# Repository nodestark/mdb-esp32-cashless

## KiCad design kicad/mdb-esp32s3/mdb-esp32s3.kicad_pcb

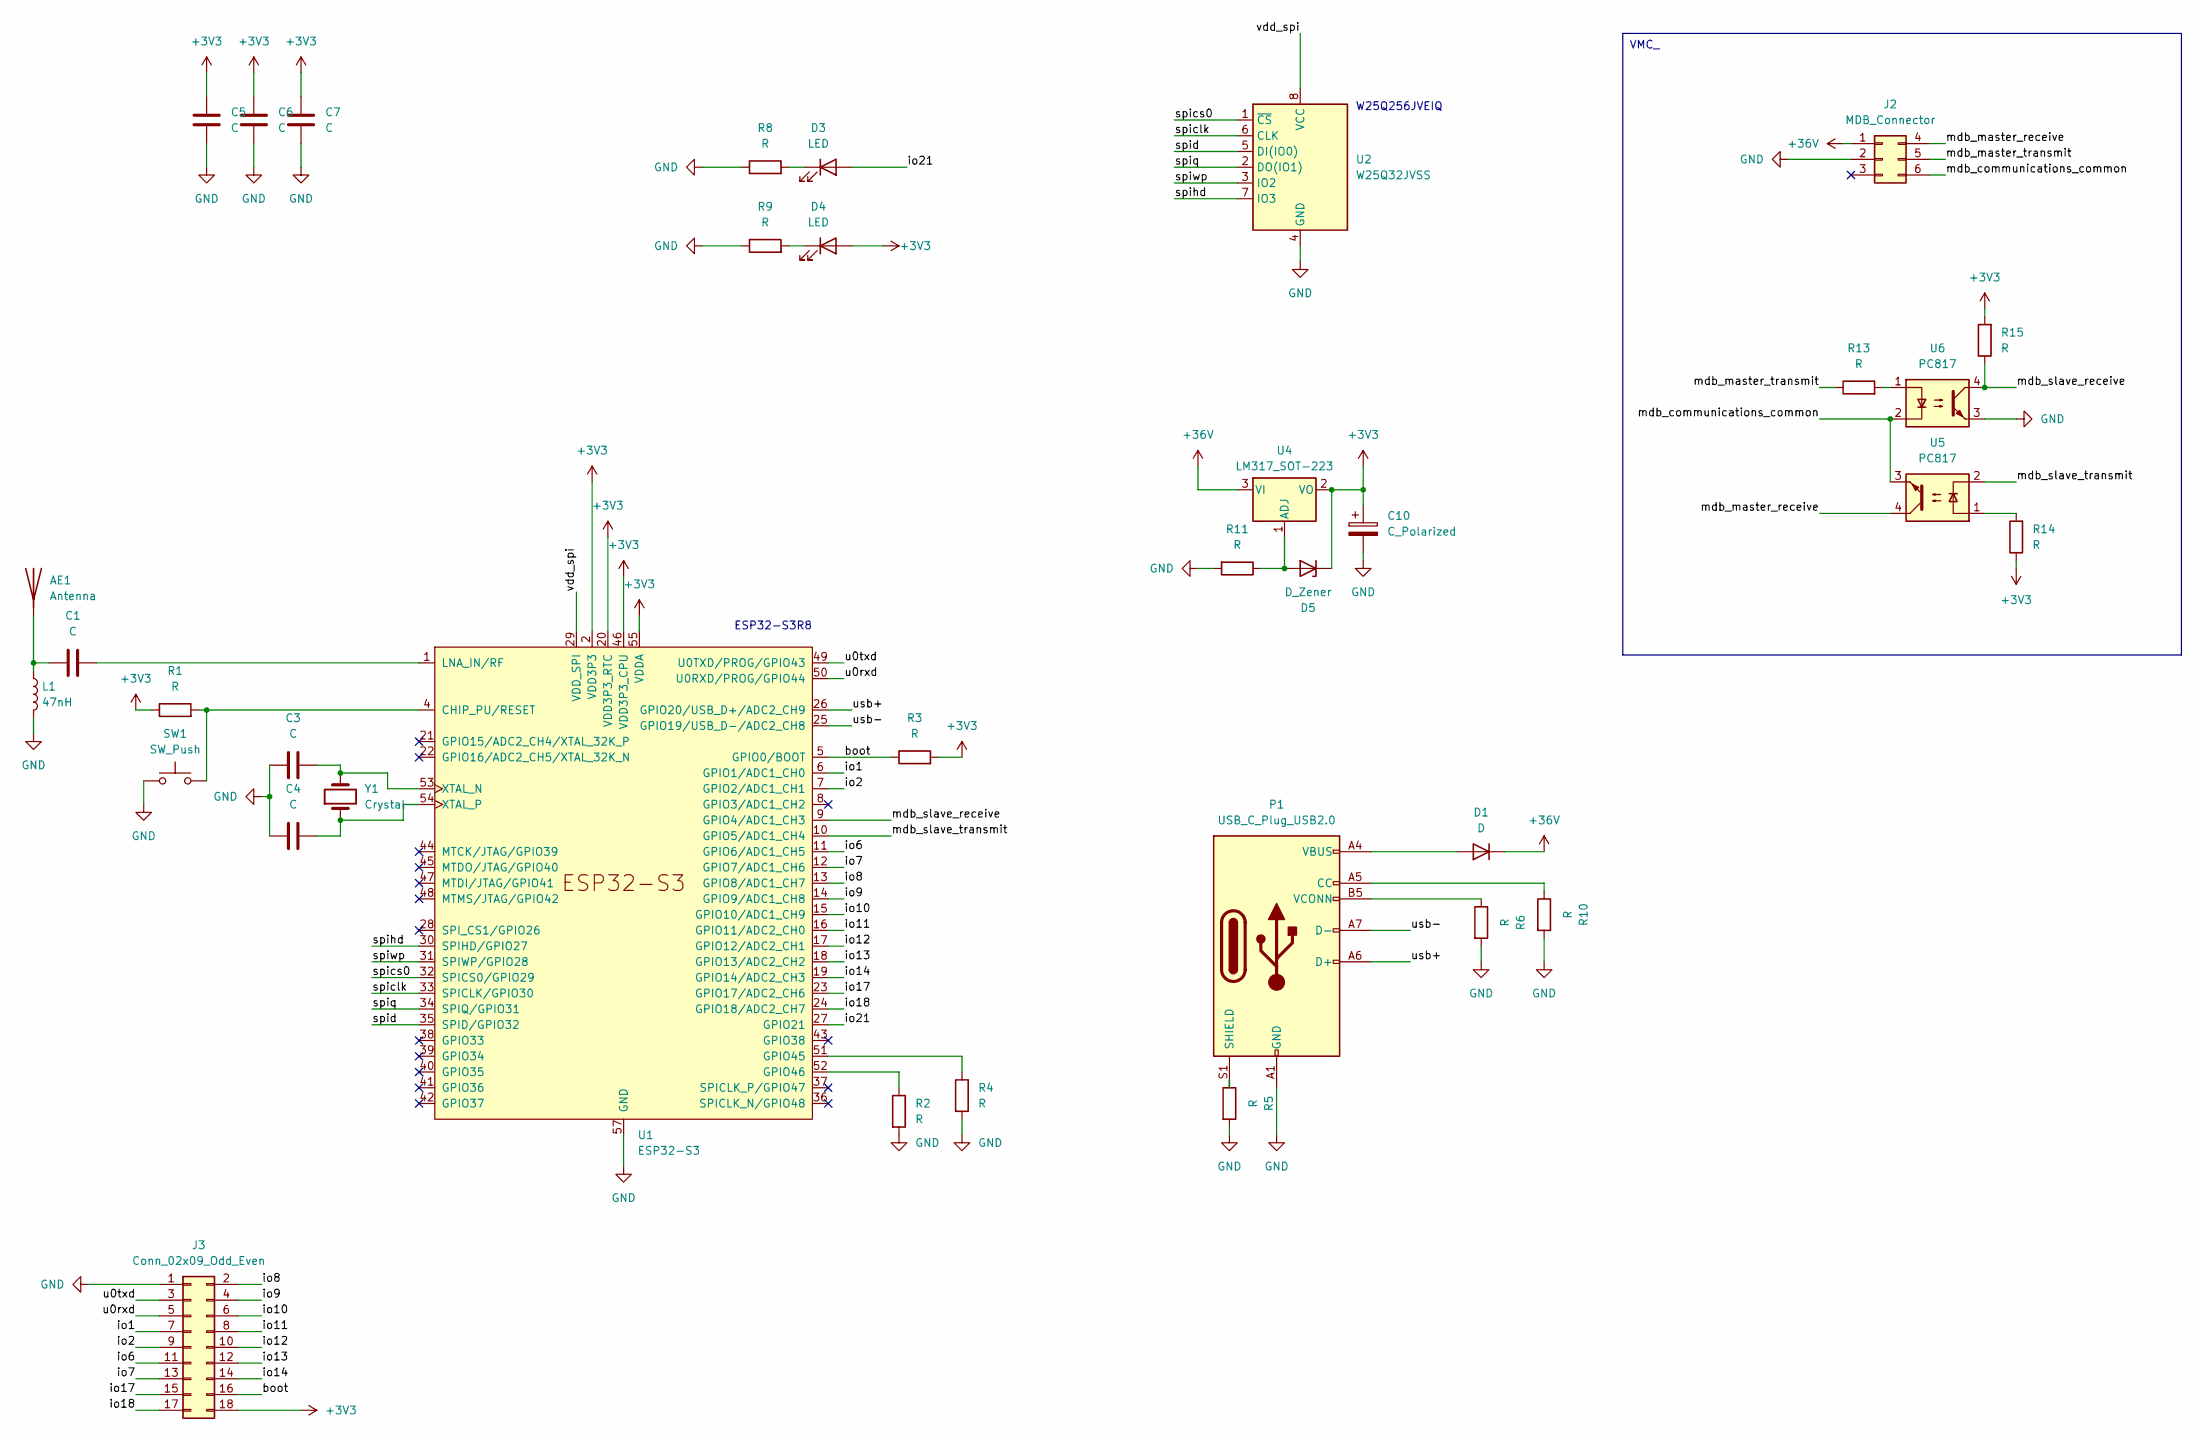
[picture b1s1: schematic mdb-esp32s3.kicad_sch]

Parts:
AE1: Antenna; Texas_SWRA117D_2.4GHz_Right
C1, C3, C4, C5, C6, C7: C; C_0603_1608Metric
C10: C_Polarized; CP_EIA-3216-18_Kemet-A
D1: D; D_SOD-123
D3, D4: LED; LED_0603_1608Metric
D5: D_Zener; D_MiniMELF
J2: MDB_Connector; Molex_Mini-Fit_Jr_5566-06A_2x03_P4.20mm_Vertical
J3: Conn_02x09_Odd_Even; PinHeader_2x09_P2.54mm_Vertical
L1: 47nH; L_0603_1608Metric
P1: USB_C_Plug_USB2.0; USB_C_Receptacle_G-Switch_GT-USB-7010ASV
R1, R2, R3, R4, R5, R6, R8, R9, R10: R; R_0603_1608Metric
R11, R13, R14, R15: R; R_0805_2012Metric
SW1: SW_Push; SW_Tactile_SPST_NO_Straight_CK_PTS636Sx25SMTRLFS
U1: ESP32-S3; QFN-56-1EP_7x7mm_P0.4mm_EP5.6x5.6mm
U2: W25Q32JVSS; WSON-8-1EP_8x6mm_P1.27mm_EP3.4x4.3mm
U4: LM317_SOT-223; SOT-223-3_TabPin2
U5, U6: PC817; DIP-4_W7.62mm
Y1: Crystal; Crystal_HC49-4H_Vertical

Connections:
+3V3: C5.2, C6.2, C7.2, C10.1, D4.2 (A), D5.1 (K), J3.18, R1.1, R3.2, R14.1, R15.2, U1.2 (VDD3P3), U1.3 (VDD3P3), U1.20 (VDD3P3_RTC), U1.46 (VDD3P3_CPU), U1.55 (VDDA), U1.56 (VDDA), U4.2 (VO)
+36V: D1.1 (K), J2.1, U4.3 (VI)
/boot: J3.16, R3.1, U1.5 (GPIO0/BOOT)
/io1: J3.7, U1.6 (GPIO1/ADC1_CH0)
/io2: J3.9, U1.7 (GPIO2/ADC1_CH1)
/io6: J3.11, U1.11 (GPIO6/ADC1_CH5)
/io7: J3.13, U1.12 (GPIO7/ADC1_CH6)
/io8: J3.2, U1.13 (GPIO8/ADC1_CH7)
/io9: J3.4, U1.14 (GPIO9/ADC1_CH8)
/io10: J3.6, U1.15 (GPIO10/ADC1_CH9)
/io11: J3.8, U1.16 (GPIO11/ADC2_CH0)
/io12: J3.10, U1.17 (GPIO12/ADC2_CH1)
/io13: J3.12, U1.18 (GPIO13/ADC2_CH2)
/io14: J3.14, U1.19 (GPIO14/ADC2_CH3)
/io17: J3.15, U1.23 (GPIO17/ADC2_CH6)
/io18: J3.17, U1.24 (GPIO18/ADC2_CH7)
/io21: D3.2 (A), U1.27 (GPIO21)
/mdb_communications_common: J2.6, U5.3, U6.2
/mdb_master_receive: J2.4, U5.4
/mdb_master_transmit: J2.5, R13.1
/mdb_slave_receive: R15.1, U1.9 (GPIO4/ADC1_CH3), U6.4
/mdb_slave_transmit: U1.10 (GPIO5/ADC1_CH4), U5.2
/spiclk: U1.33 (SPICLK/GPIO30), U2.6 (CLK)
/spics0: U1.32 (SPICS0/GPIO29), U2.1 (~CS)
/spid: U1.35 (SPID/GPIO32), U2.5 (DI(IO0))
/spihd: U1.30 (SPIHD/GPIO27), U2.7 (IO3)
/spiq: U1.34 (SPIQ/GPIO31), U2.2 (DO(IO1))
/spiwp: U1.31 (SPIWP/GPIO28), U2.3 (IO2)
/u0rxd: J3.5, U1.50 (U0RXD/PROG/GPIO44)
/u0txd: J3.3, U1.49 (U0TXD/PROG/GPIO43)
/usb+: P1.A6 (D+), U1.26 (GPIO20/USB_D+/ADC2_CH9)
/usb-: P1.A7 (D-), U1.25 (GPIO19/USB_D-/ADC2_CH8)
/vdd_spi: U1.29 (VDD_SPI), U2.8 (VCC)
GND: C3.1, C4.1, C5.1, C6.1, C7.1, C10.2, J2.2, J3.1, L1.2, P1.A1 (GND), P1.A12 (GND), P1.B1 (GND), P1.B12 (GND), R2.2, R4.2, R5.2, R6.2, R8.1, R9.1, R10.2, R11.2, SW1.1, U1.57 (GND), U2.4 (GND), U6.3
unnamed: AE1.1 (A), C1.1, L1.1
unnamed: D1.2 (A), P1.A4 (VBUS), P1.A9 (VBUS), P1.B4 (VBUS), P1.B9 (VBUS)
unnamed: D3.1 (K), R8.2
unnamed: D4.1 (K), R9.2
unnamed: D5.2 (A), R11.1, U4.1 (ADJ)
unnamed: P1.A5 (CC), R10.1
unnamed: P1.S1 (SHIELD), R5.1
unnamed: P1.B5 (VCONN), R6.1
unnamed: R13.2, U6.1
unnamed: R14.2, U5.1
unnamed: R1.2, SW1.2, U1.4 (CHIP_PU/RESET)
unnamed: R4.1, U1.51 (GPIO45)
unnamed: R2.1, U1.52 (GPIO46)
unnamed: C1.2, U1.1 (LNA_IN/RF)
unnamed: C3.2, U1.53 (XTAL_N), Y1.2
unnamed: C4.2, U1.54 (XTAL_P), Y1.1

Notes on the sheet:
VMC_
ESP32-S3R8
W25Q256JVEIQ

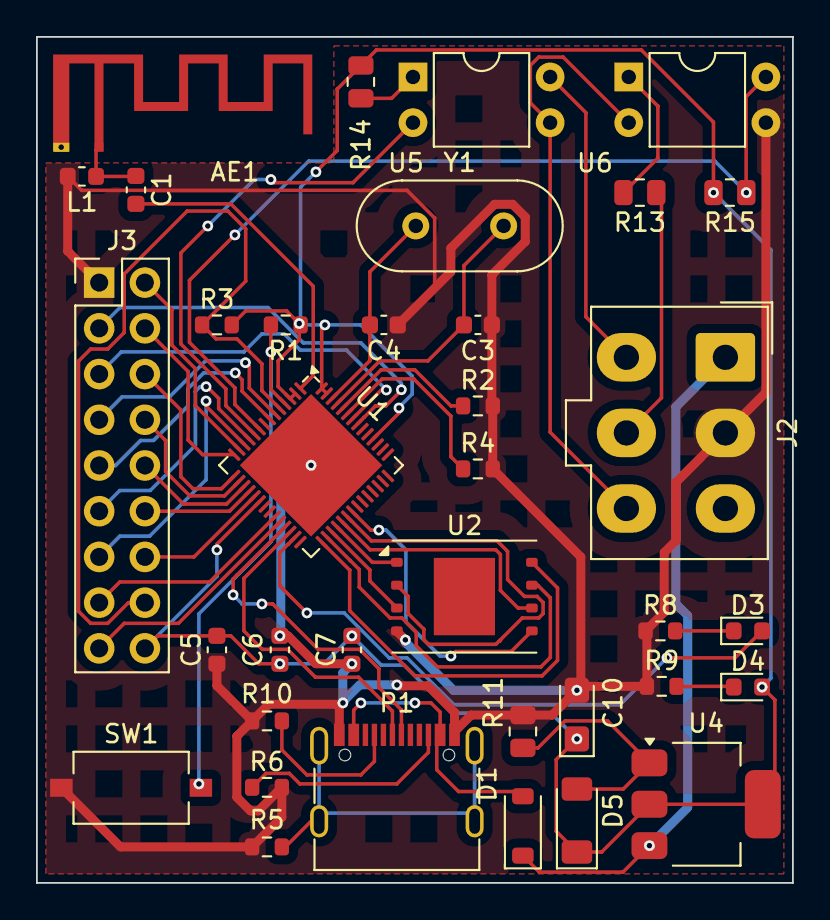
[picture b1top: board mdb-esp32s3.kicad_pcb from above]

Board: 2 copper layers, 42.0 x 47.0 mm, 36 parts (0 on the bottom side), 50 nets.
